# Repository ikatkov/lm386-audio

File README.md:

# Small audio amplifier

This is LM386-based power amplifier for radio projects. The simplest possible design directly from the datasheet. 

Assembled mostly from salvaged parts and parts of dubious origin.

The charging module and USB socket are not shown on PCB. I had a USB micro socket breakout that I screw directly to the top right corner. USB socket has to stick out from the main board otherwise wide jacks do not fit. The charging module is mounted vertically facing the back panel so that LEDs are visible through the hole.

# Notes

Instead of a hard-to-get 10k logarithmic volume pot, there is a 100k linear with a 12k resistor from the pot wiper to the ground. This is a nice trick.

The output audio signal jack is wired to disconnect the speaker when something, typically headphones, is inserted.

There is a lipo battery inside, with a TP4056 module. The standard PCB was modified for load sharing i.e. when USB power is available, it powers the amplifier directly, bypassing the battery. A  5V boost module

was modified for ~12V. Output voltage ripple is ~ 50mV. I presume it is much larger under the load, but the audio amplifier load is very jittery and nonstable as well. LM386 is 0.5W max anyway.

# Enclosure

See 3D printed enclosure files [here](enclosure)

The volume potentiometer stem is not shown. I now assemble first and drill all the holes later. This is significantly faster than high-precision measuring and assembly. 

# Assembly

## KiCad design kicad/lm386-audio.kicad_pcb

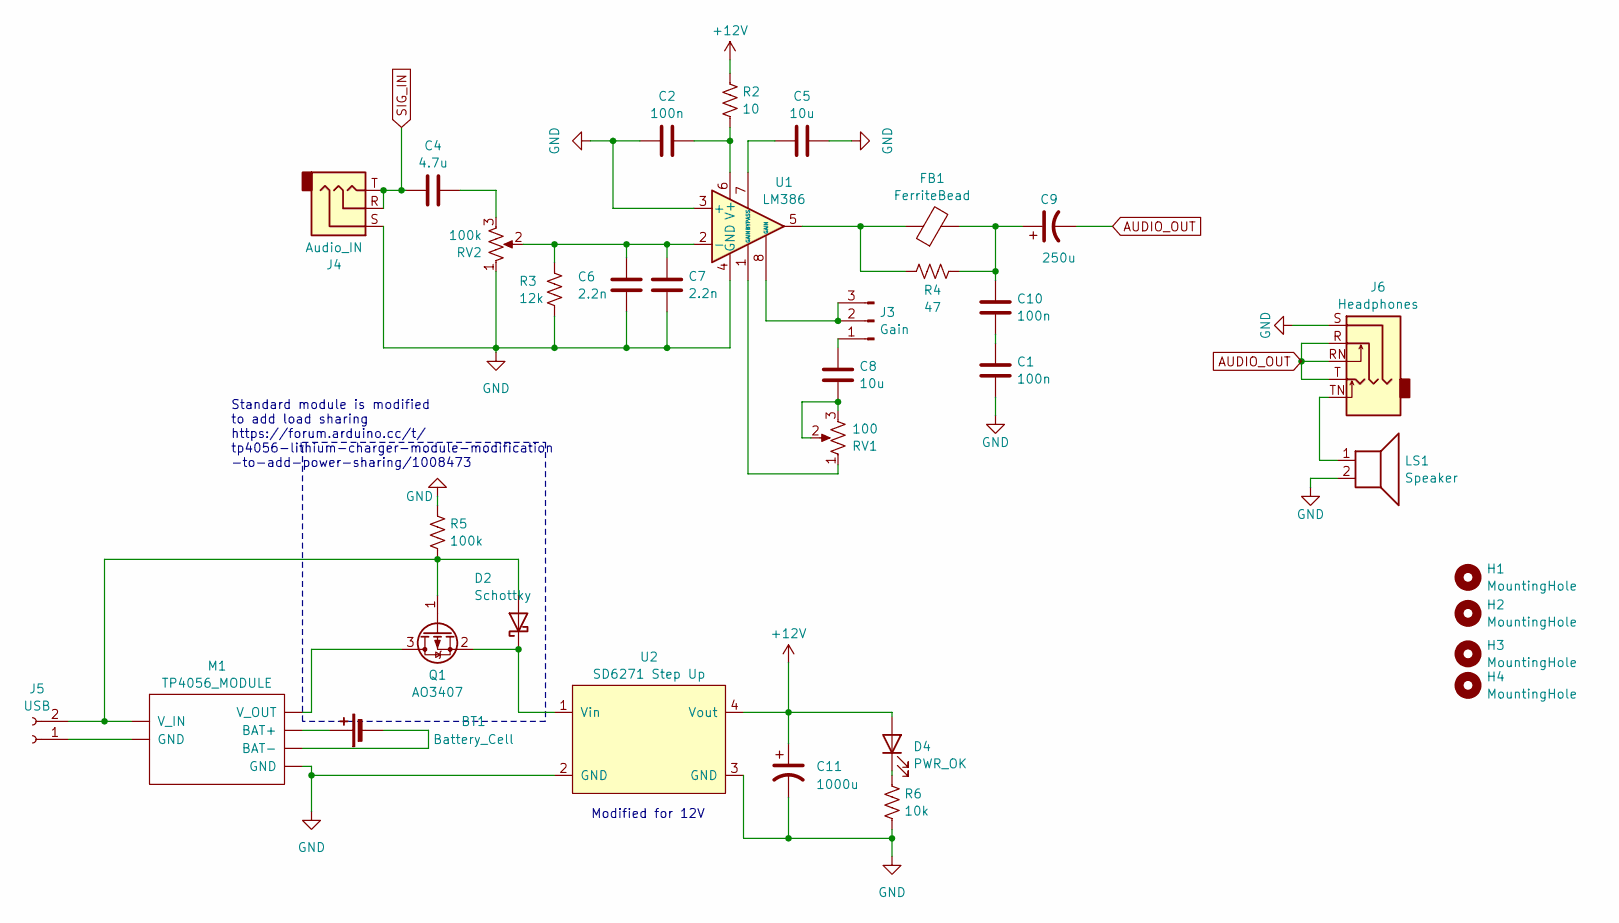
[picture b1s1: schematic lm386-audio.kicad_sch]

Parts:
BT1: Battery_Cell
C1, C2, C10: 100n; C_1206_3216Metric
C4: 4.7u; C_1206_3216Metric
C5, C8: 10u; C_1206_3216Metric
C6, C7: 2.2n; C_1206_3216Metric
C9: 250u; CP_Radial_D5.0mm_P2.50mm
C11: 1000u; CP_Radial_D10.0mm_P2.50mm
D2: Schottky; D_SMA
D4: PWR_OK; LED_D5.0mm
FB1: FerriteBead; R_0805_2012Metric
H1, H2, H3, H4: MountingHole; MountingHole_3.2mm_M3
J3: Gain; PinHeader_1x03_P2.54mm_Vertical
J4: Audio_IN; Jack_3.5mm_CUI_SJ1-3533NG_Horizontal
J5: USB
J6: Headphones; Jack_3.5mm_CUI_SJ1-3535NG_Horizontal
LS1: Speaker; PinHeader_1x02_P2.54mm_Vertical
M1: TP4056_MODULE; TP4056-18650
Q1: AO3407; SOT-23
R2: 10; R_0805_2012Metric
R3: 12k; R_0805_2012Metric
R4: 47; R_0805_2012Metric
R5: 100k; R_0805_2012Metric
R6: 10k; R_0805_2012Metric
RV1: 100; Potentiometer_Runtron_RM-065_Vertical
RV2: 100k; Potentiometer_Alps_RK09Y11_Single_Horizontal
U1: LM386; DIP-8_W7.62mm_Socket_LongPads
U2: SD6271 Step Up; SD6271_StepUp

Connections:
+12V: C11.1, D4.2 (A), R2.1, U2.4 (Vout)
AUDIO_OUT: C9.2, J6.R, J6.RN, J6.T
GND: C1.1, C2.1, C5.1, C6.1, C7.1, C11.2, J4.S, J6.S, LS1.2, M1.4 (GND), R3.1, R5.2, R6.2, RV2.1, U1.3 (+), U1.4 (GND), U2.2 (GND), U2.3 (GND)
unnamed: BT1.1 (+), M1.5 (BAT+)
unnamed: BT1.2 (-), M1.6 (BAT-)
unnamed: C1.2, C10.1
unnamed: C4.2, RV2.3
unnamed: C8.1, RV1.2, RV1.3
unnamed: C9.1, C10.2, FB1.2, R4.2
unnamed: D2.2 (A), J5.2, M1.1 (V_IN), Q1.1 (G), R5.1
unnamed: D2.1 (K), Q1.2 (S), U2.1 (Vin)
unnamed: D4.1 (K), R6.1
unnamed: FB1.1, R4.1, U1.5
unnamed: C8.2, J3.1
unnamed: J3.2, J3.3, U1.8 (GAIN)
unnamed: J5.1, M1.2 (GND)
unnamed: J6.TN, LS1.1
unnamed: M1.3 (V_OUT), Q1.3 (D)
unnamed: RV1.1, U1.1 (GAIN)
unnamed: C6.2, C7.2, R3.2, RV2.2, U1.2 (-)
unnamed: C5.2, U1.7 (BYPASS)
unnamed: C2.2, R2.2, U1.6 (V+)
SIG_IN: C4.1, J4.R, J4.T

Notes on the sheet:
Standard module is modified to add load sharing https://forum.arduino.cc/t/ tp4056-lithium-charger-module-modification -to-add-power-sharing/1008473
Modified for 12V

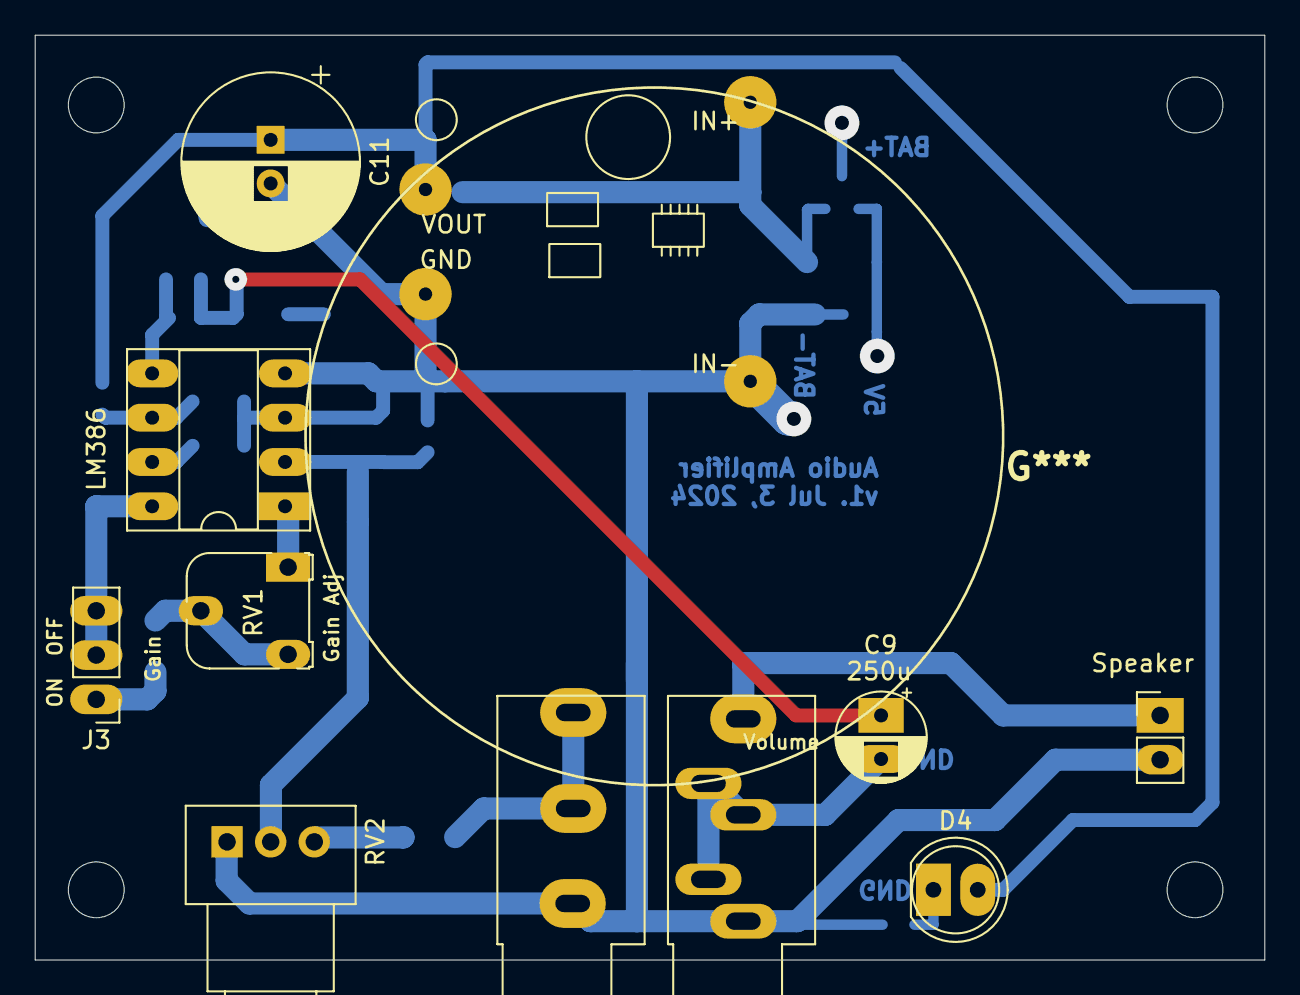
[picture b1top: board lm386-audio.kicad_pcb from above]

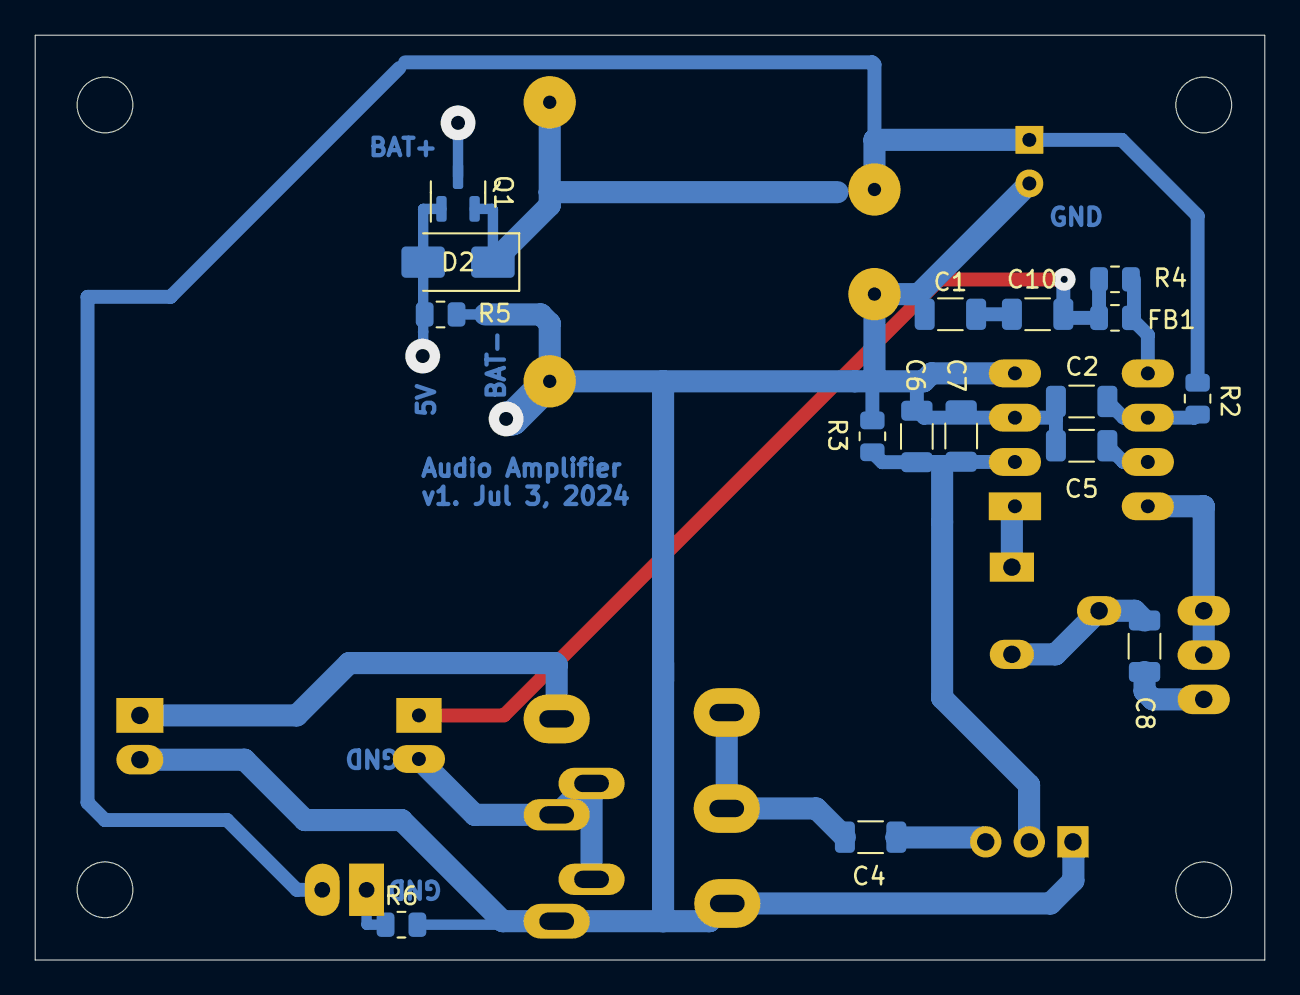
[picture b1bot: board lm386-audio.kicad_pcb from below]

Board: 4 copper layers, 70.5 x 53.0 mm, 31 parts (16 on the bottom side), 19 nets.

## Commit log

2024-07-07 clean up + documentation
2024-07-07 add photo
2024-07-07 More readme
